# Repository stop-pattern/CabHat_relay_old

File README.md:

# CabHat_relay
リレー拡張基板

## 入力
- grove
- hat(stack)

##

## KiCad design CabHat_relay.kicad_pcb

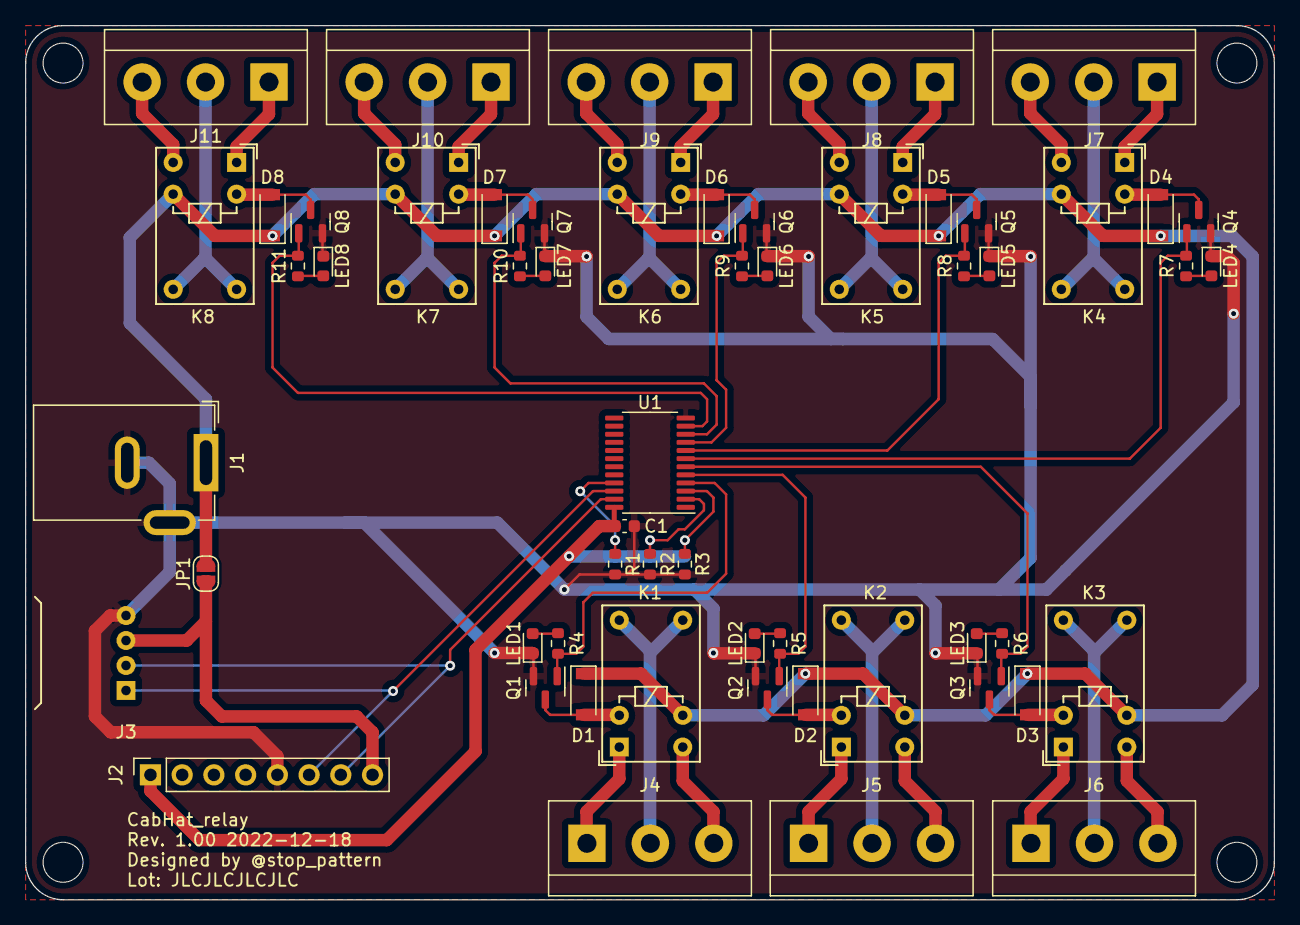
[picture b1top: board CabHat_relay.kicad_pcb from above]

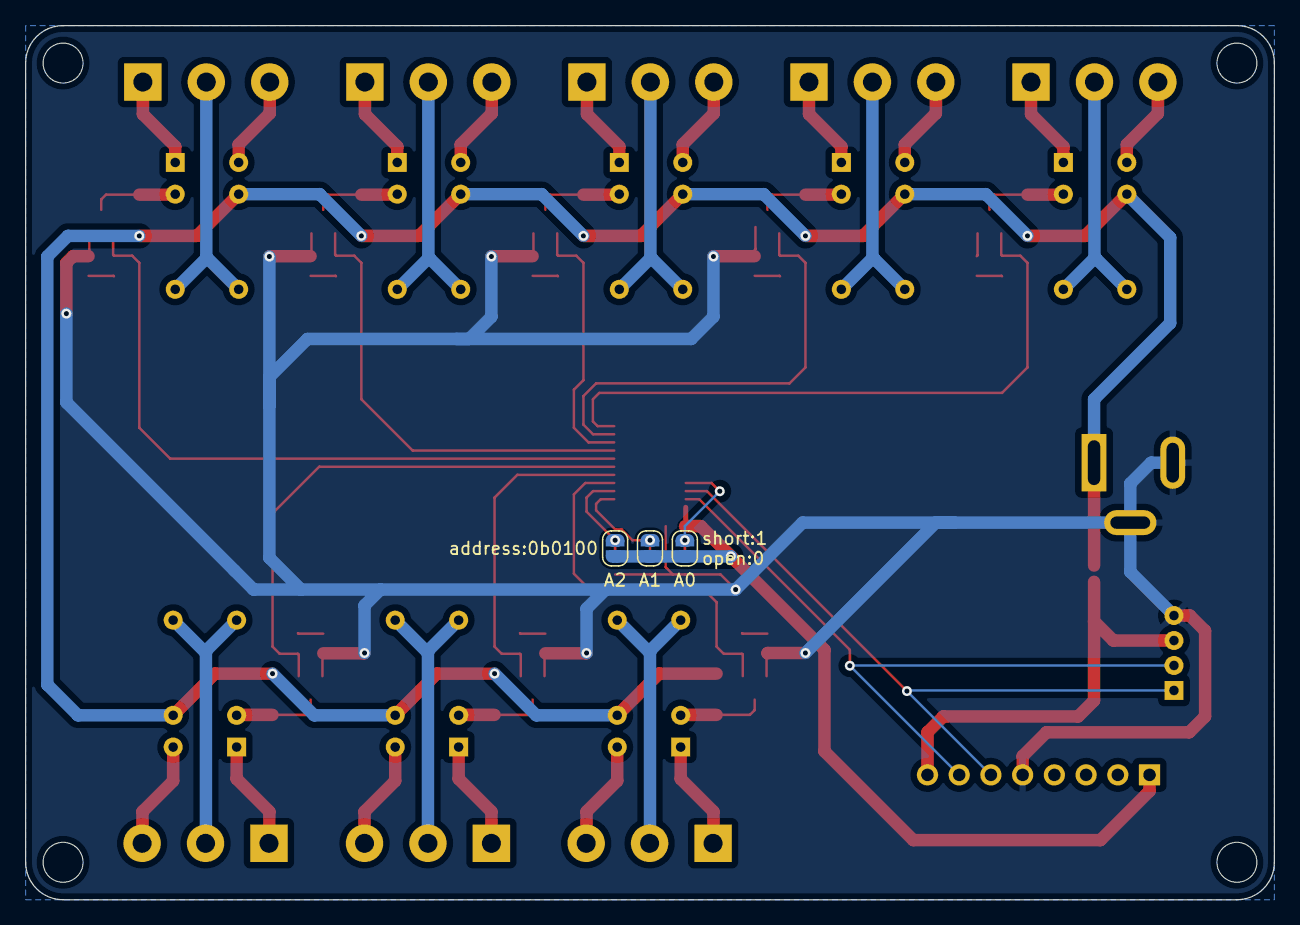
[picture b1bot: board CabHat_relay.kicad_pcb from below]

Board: 2 copper layers, 100.0 x 70.0 mm, 64 parts (3 on the bottom side), 57 nets.

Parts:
C1: 100n; C_0603_1608Metric
D1, D2, D3, D4, D5, D6, D7, D8: D; D_SOD-123
J1: Barrel_Jack_Switch; BarrelJack_GCT_DCJ200-10-A_Horizontal
J2: Conn_01x08; PinSocket_1x08_P2.54mm_Vertical
J3: Conn_01x04; Grove_1x04_P2mm_Horizontal_silk_inside
J4, J5, J6, J7, J8, J9, J10, J11: Screw_Terminal_01x03; TerminalBlock_akizuki_TB111_P5.08mm
JP1, JP2, JP3, JP4: SolderJumper_2_Open; SolderJumper-2_P1.3mm_Open_RoundedPad1.0x1.5mm
K1, K2, K3, K4, K5, K6, K7, K8: Y14x-1C-xxDS; Relay_SPDT_HsinDa_Y14
LED1, LED2, LED3, LED4, LED5, LED6, LED7, LED8: LED; LED_0603_1608Metric
Q1, Q2, Q3, Q4, Q5, Q6, Q7, Q8: Q_NMOS_GSD; SOT-23
R1, R2, R3, R4, R5, R6, R7, R8, R9, R10, R11: 10k; R_0603_1608Metric
REF0, REF1, REF2, REF3: MountingHole_3.2mm_M3
U1: PCA9555PW; TSSOP-24_4.4x7.8mm_P0.65mm

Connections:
+3V3: C1.1, J2.1, JP2.2 (B), JP3.2 (B), JP4.2 (B), U1.24 (VDD)
+5V: J2.8, J3.3, JP1.1 (A)
+VSW: D1.1 (K), D2.1 (K), D3.1 (K), D4.1 (K), D5.1 (K), D6.1 (K), D7.1 (K), D8.1 (K), J1.1, JP1.2 (B), K1.4, K2.4, K3.4, K4.4, K5.4, K6.4, K7.4, K8.4
/A0: JP2.1 (A), R1.1, U1.21 (A0)
/A1: JP3.1 (A), R2.1, U1.2 (A1)
/A2: JP4.1 (A), R3.1, U1.3 (A2)
/SCL: J2.6, J3.1, U1.22 (SCL)
/SDA: J2.7, J3.2, U1.23 (SDA)
/relay00/COM: J4.2, K1.5, K1.6
/relay00/N.C.: J4.3, K1.2
/relay00/N.O.: J4.1, K1.1
/relay01/COM: J5.2, K2.5, K2.6
/relay01/N.C.: J5.3, K2.2
/relay01/N.O.: J5.1, K2.1
/relay02/COM: J6.2, K3.5, K3.6
/relay02/N.C.: J6.3, K3.2
/relay02/N.O.: J6.1, K3.1
/relay03/COM: J7.2, K4.5, K4.6
/relay03/N.C.: J7.3, K4.2
/relay03/N.O.: J7.1, K4.1
/relay04/COM: J8.2, K5.5, K5.6
/relay04/N.C.: J8.3, K5.2
/relay04/N.O.: J8.1, K5.1
/relay05/COM: J9.2, K6.5, K6.6
/relay05/N.C.: J9.3, K6.2
/relay05/N.O.: J9.1, K6.1
/relay06/COM: J10.2, K7.5, K7.6
/relay06/N.C.: J10.3, K7.2
/relay06/N.O.: J10.1, K7.1
/relay07/COM: J11.2, K8.5, K8.6
/relay07/N.C.: J11.3, K8.2
/relay07/N.O.: J11.1, K8.1
GND: C1.2, J1.2, J1.3, J2.5, J3.4, LED1.1 (K), LED2.1 (K), LED3.1 (K), LED4.1 (K), LED5.1 (K), LED6.1 (K), LED7.1 (K), LED8.1 (K), Q1.2 (S), Q2.2 (S), Q3.2 (S), Q4.2 (S), Q5.2 (S), Q6.2 (S), Q7.2 (S), Q8.2 (S), R1.2, R2.2, R3.2, U1.12 (VSS)
unnamed: D1.2 (A), K1.3, Q1.3 (D)
unnamed: D2.2 (A), K2.3, Q2.3 (D)
unnamed: D3.2 (A), K3.3, Q3.3 (D)
unnamed: D4.2 (A), K4.3, Q4.3 (D)
unnamed: D5.2 (A), K5.3, Q5.3 (D)
unnamed: D6.2 (A), K6.3, Q6.3 (D)
unnamed: D7.2 (A), K7.3, Q7.3 (D)
unnamed: D8.2 (A), K8.3, Q8.3 (D)
unnamed: LED1.2 (A), R4.2
unnamed: LED2.2 (A), R5.2
unnamed: LED3.2 (A), R6.2
unnamed: LED4.2 (A), R7.2
unnamed: LED5.2 (A), R8.2
unnamed: LED6.2 (A), R9.2
unnamed: LED7.2 (A), R10.2
unnamed: LED8.2 (A), R11.2
ex.IO0_0: Q1.1 (G), R4.1, U1.4 (IO0_0)
ex.IO0_1: Q2.1 (G), R5.1, U1.5 (IO0_1)
ex.IO0_2: Q3.1 (G), R6.1, U1.6 (IO0_2)
ex.IO0_3: Q4.1 (G), R7.1, U1.7 (IO0_3)
ex.IO0_4: Q5.1 (G), R8.1, U1.8 (IO0_4)
ex.IO0_5: Q6.1 (G), R9.1, U1.9 (IO0_5)
ex.IO0_6: Q7.1 (G), R10.1, U1.10 (IO0_6)
ex.IO0_7: Q8.1 (G), R11.1, U1.11 (IO0_7)

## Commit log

2022-12-10 Create LICENSE
2022-12-11 sch v0.01
2022-12-18 v1.00
